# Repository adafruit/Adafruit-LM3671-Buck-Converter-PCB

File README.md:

## Adafruit LM3671 Buck Converter PCB
<a href="http://www.adafruit.com/products/2745"><br/>
Click here to purchase one from the Adafruit shop</a>

Your power supply problems just got SUPER SOLVED! This 3.3V Buck Converter Breakout board is great for supplying power to low voltage circuits from a single Li-Ion cell battery or USB power.  This chip provides up to 600-mA load current across the entire input voltage range of 3.5 to 5.5V.  Great for your portable project, we made this "pin compatible" with the LM1117-3.3V TO-220 chip so you can swap it in for better performance (90-95% efficiency!) There's also an ENable pin, tie it low to shut down the output completely.

There's a 2-MHz fixed-frequency in PWM mode and PFM mode extends the battery life by reducing the current during light load or standby operation.

PCB files for Adafruit LM3671 Buck Converter. The format is EagleCAD schematic and board layout
- https://www.adafruit.com/product/2745

### License

Adafruit invests time and resources providing this open source design, please support Adafruit and open-source hardware by purchasing products from [Adafruit](https://www.adafruit.com)!

All text above must be included in any redistribution

Designed by Limor Fried/Ladyada for Adafruit Industries.
Creative Commons Attribution/Share-Alike, all text above must be included in any redistribution. 
See license.txt for additional information.

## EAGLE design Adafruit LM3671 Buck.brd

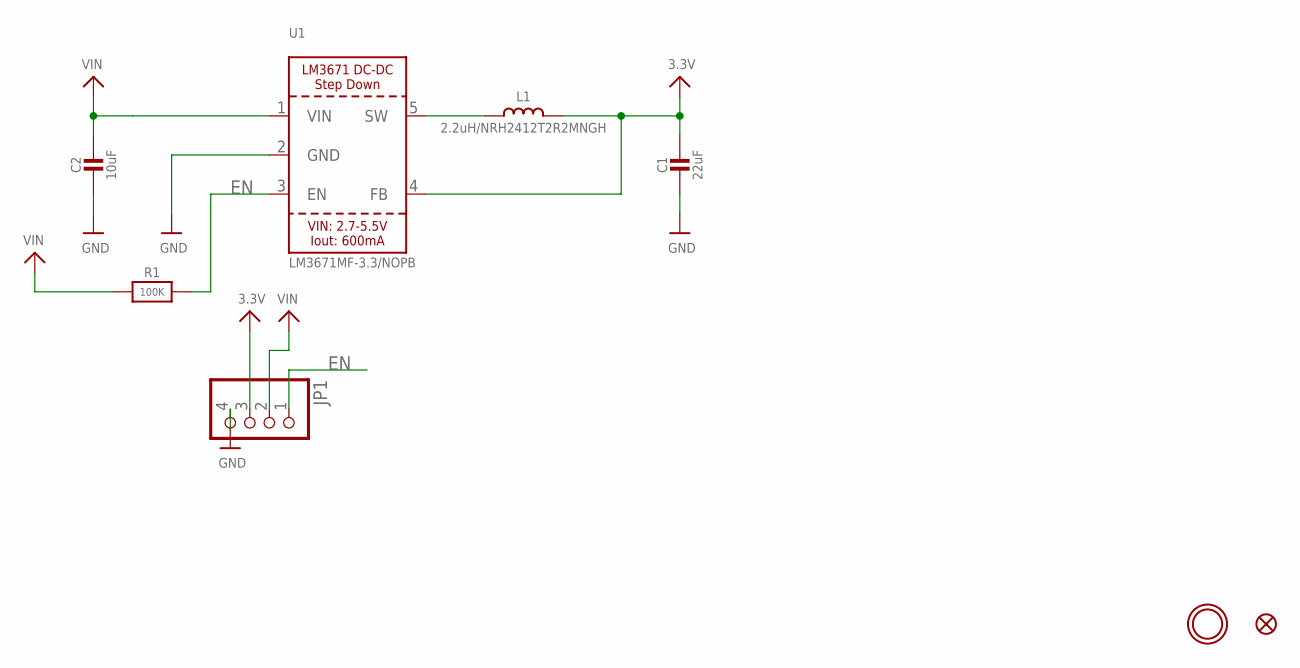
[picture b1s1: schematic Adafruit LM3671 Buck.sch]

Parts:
C1: 22uF; 0805-NO
C2: 10uF; 0805-NO
FID1: FIDUCIAL""; FIDUCIAL_1MM
JP1: HEADER-1X4ROUND; 1X04_ROUND
L1: 2.2uH/NRH2412T2R2MNGH; INDUCTOR_TAIYOYUDEN_NRH2412T
R1: 100K; 0805-NO
U1: LM3671MF-3.3/NOPB; SOT23-5
U$9: MOUNTINGHOLE2.5; MOUNTINGHOLE_2.5_PLATED

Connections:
3.3V: C1.1, JP1.3, L1.2, U1.4 (FB)
EN: JP1.1, R1.2, U1.3 (EN)
GND: C1.2, C2.2, JP1.4, U1.2 (GND)
unnamed: L1.1, U1.5 (SW)
VIN: C2.1, JP1.2, R1.1, U1.1 (VIN)

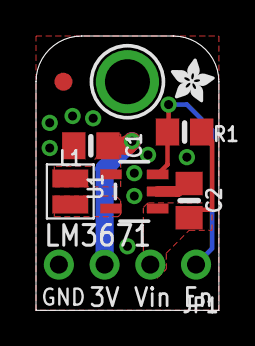
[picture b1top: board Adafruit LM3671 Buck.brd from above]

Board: 2 copper layers, 10.2 x 15.2 mm, 10 parts (1 on the bottom side), 5 nets.

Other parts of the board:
U$10: PCBFEAT-REV-040
U$11: ADAFRUIT_2.5MM

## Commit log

2015-12-02 init

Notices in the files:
parts and their libraries:
microbuilder: This work is placed in the public domain, and may be freely used for commercial and non-commercial work with the following conditions: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
